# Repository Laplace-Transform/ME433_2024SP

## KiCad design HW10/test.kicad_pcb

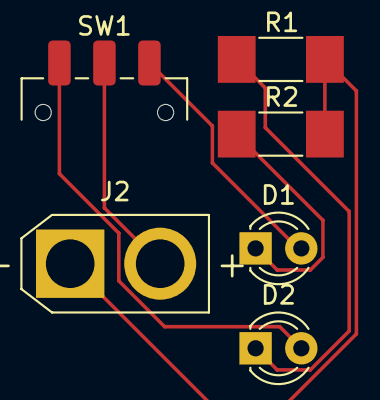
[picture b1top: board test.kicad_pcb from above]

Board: 2 copper layers, 6 parts (0 on the bottom side), 6 nets.

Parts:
D1: LED_YELLOW; LED_D3.0mm_FlatTop
D2: LED_RED; LED_D3.0mm_FlatTop
J2: Conn_01x02_Pin; AMASS_XT30U-F_1x02_P5.0mm_Vertical
R1, R2: 330; R_MELF_MMB-0207
SW1: SW_SPDT; SW_SPDT_CK_JS102011SAQN

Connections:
GND: J2.1, R1.2, R2.2
unnamed: D1.2 (A), SW1.3 (C)
unnamed: D1.1 (K), R2.1
unnamed: D2.2 (A), SW1.1 (A)
unnamed: D2.1 (K), R1.1
VCC: J2.2, SW1.2 (B)

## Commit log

2024-04-04 Create now
2024-04-04 Test
2024-05-15 HW14
2024-05-19 HW15
2024-05-20 HW12
2024-05-21 HW16
2024-05-28 HW17
2024-05-28 HW11
2024-05-29 HW10
